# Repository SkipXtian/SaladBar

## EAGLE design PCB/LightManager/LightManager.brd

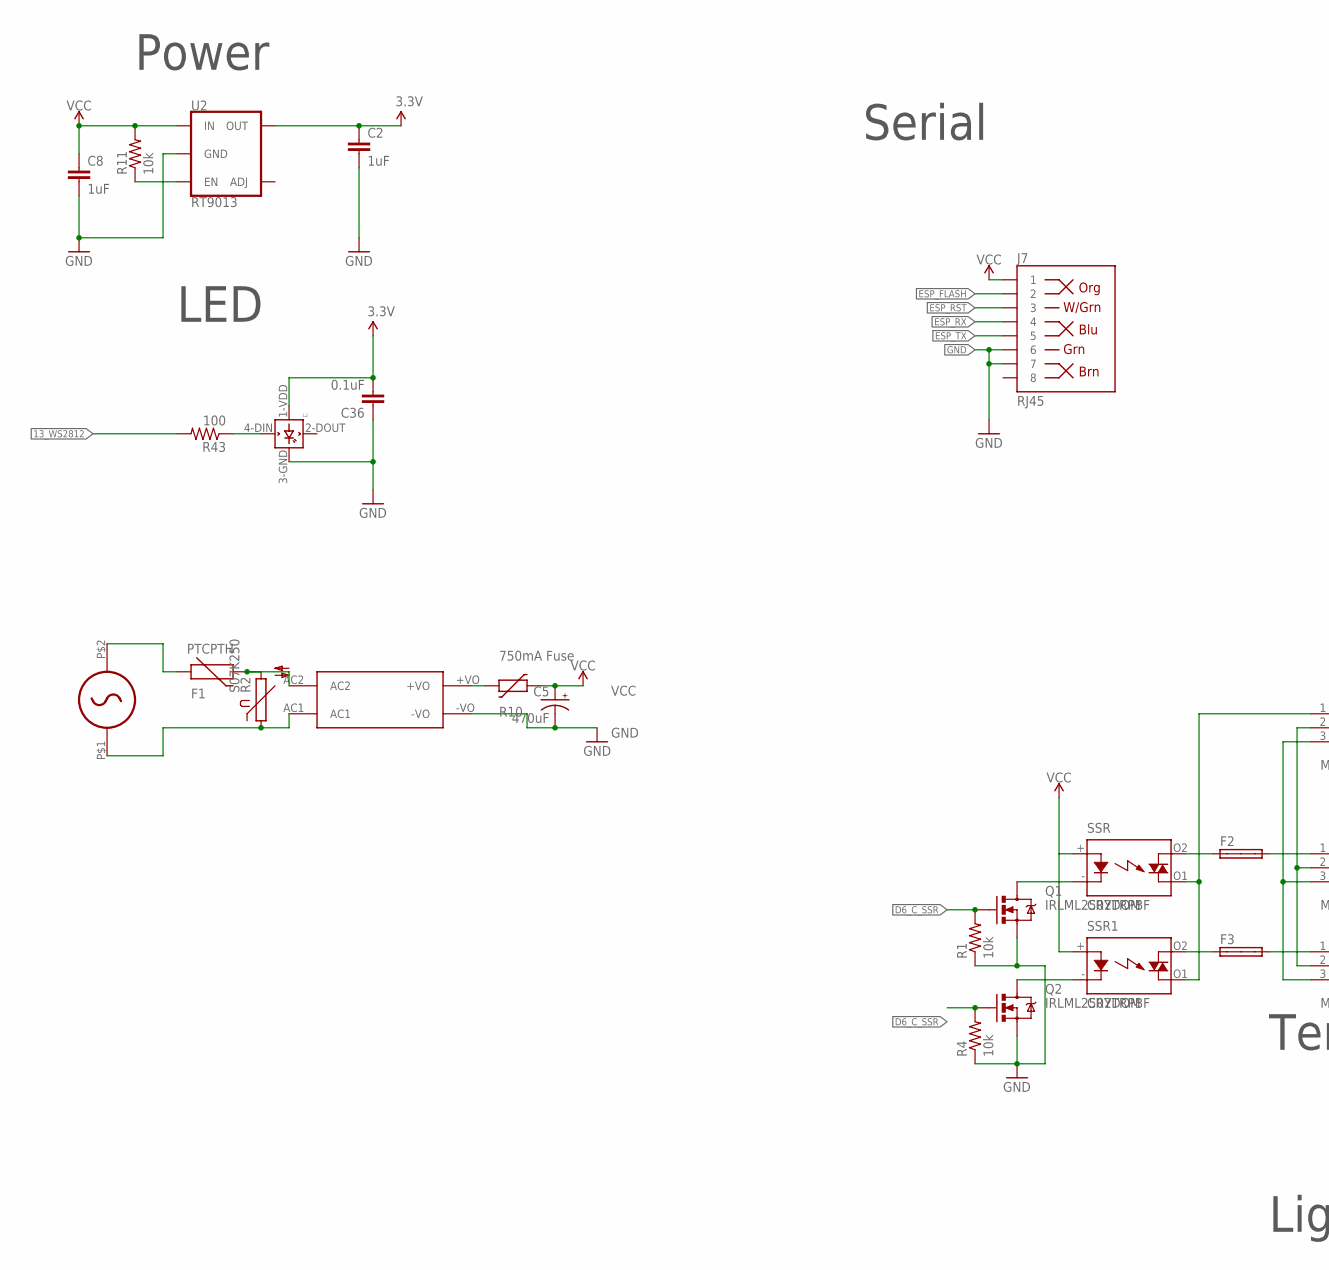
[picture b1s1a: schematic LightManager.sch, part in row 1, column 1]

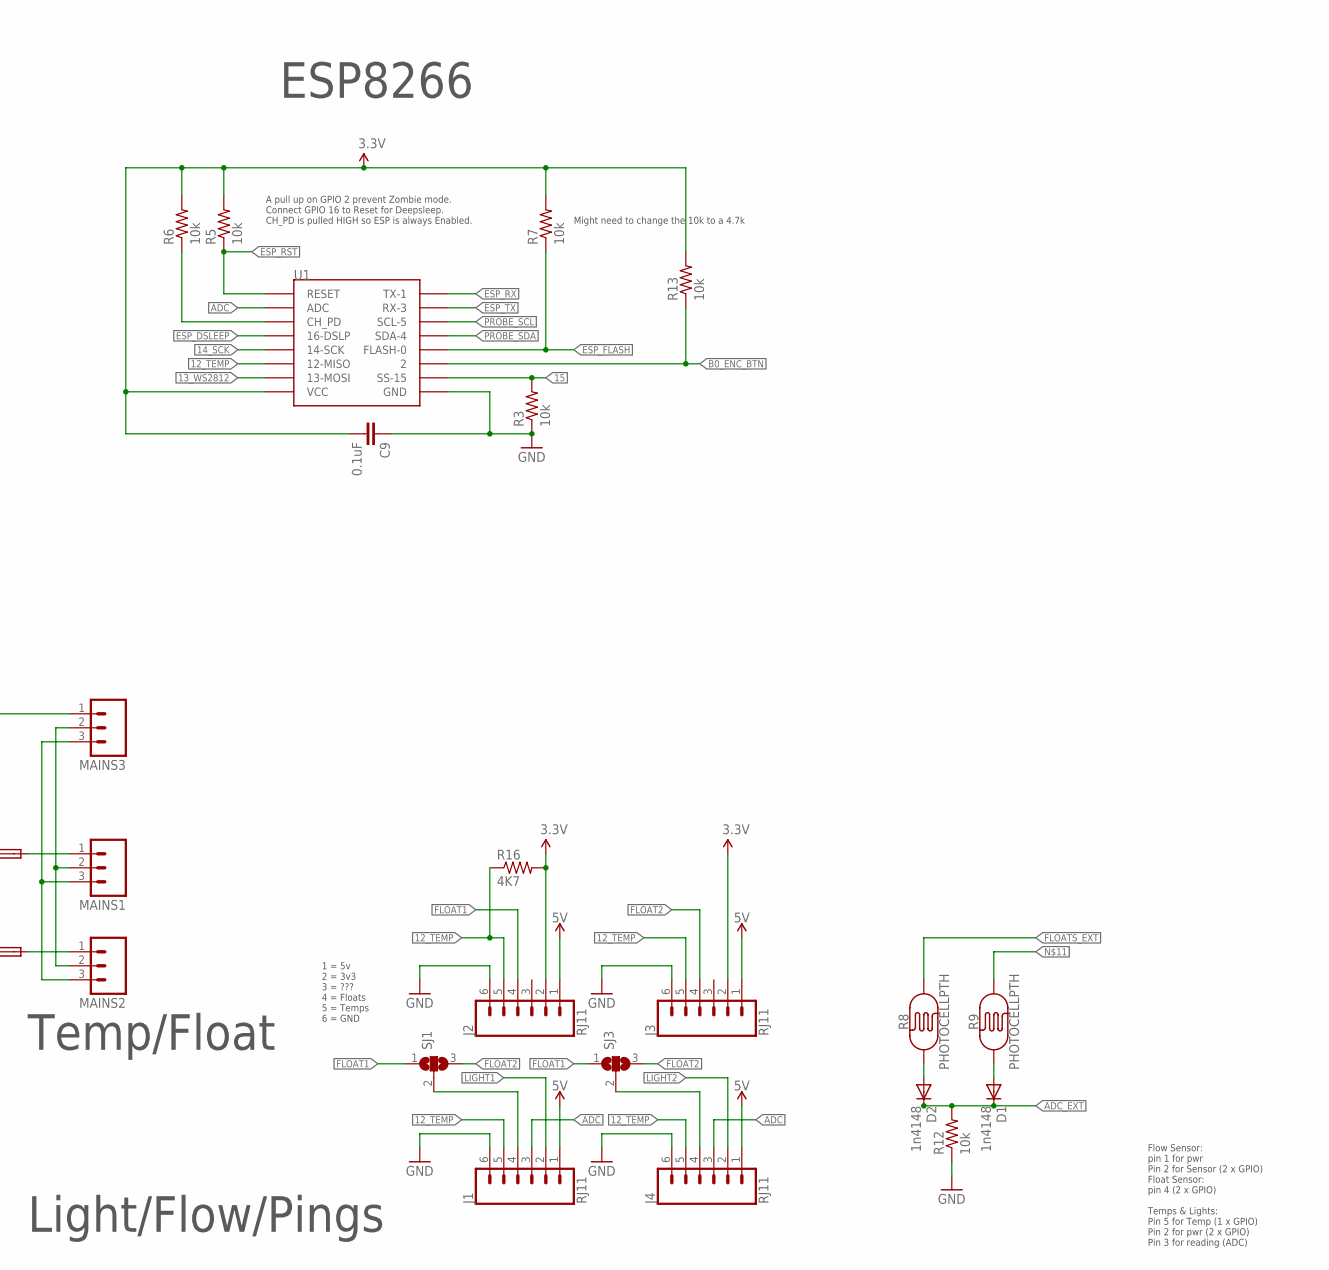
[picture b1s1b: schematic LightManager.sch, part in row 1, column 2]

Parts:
C2, C8: 1uF; 0805
C5: 470uF; PANASONIC_E
C9, C36: 0.1uF; 0805
D1, D2: 1n4148; SOD-323
F1: PTCPTH; PTC
F2, F3: SHK20L
J1, J2, J3, J4: RJ11; RJ11-6
J7: RJ45; RJ45-8
L2: WS2812B
MAINS1, MAINS2, MAINS3: M03-SCREW-5MM; SCREWTERMINAL-5MM-3
Q1, Q2: IRLML2502TRPBF; SOT23-3
R1, R3, R4, R5, R6, R7, R11, R12, R13: 10k; 0805
R2: S07K250
R8, R9: PHOTOCELLPTH; PHOTOCELL
R10: 750mA Fuse; CT/CN0805
R16: 4K7; 0805
R43: 100; 0805
SJ1, SJ3: SJ2W; SJ_2
SSR: CRYDOM; AQG
SSR1: CRYDOM; AQG; MPN AQG22224
U1: ESP12SMD; ESP12-SMD
U2: RT9013; SOT23-5
U$1: HLK-PM01
U$9: IEC320-C8

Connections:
3.3V: J2.2, J3.2, R16.2
5V: J1.1, J2.1, J3.1, J4.1
12_TEMP: J1.5, J2.5, J3.5, J4.5, R16.1, U1.GPIO12 (12-MISO)
13_WS2812: R43.2, U1.GPIO13 (13-MOSI)
14_SCK: U1.GPIO14 (14-SCK)
15: R3.2, U1.GPIO15 (SS-15)
ADC: J1.3, J4.3, U1.ADC
ADC_EXT: D1.1 (C), D2.1 (C), R12.2
B0_ENC_BTN: R13.1, U1.GPIO2 (2)
D6_C_SSR: Q1.1 (G), Q2.1 (G), R1.2, R4.2
ESP_3.3V: C2.1, C9.2, C36.2, L2.1-VDD (VDD), R5.2, R6.2, R7.2, R13.2, U1.VCC, U2.5 (OUT)
ESP_DSLEEP: U1.GPIO16 (16-DSLP)
ESP_FLASH: J7.2, R7.1, U1.GPIO0 (FLASH-0)
ESP_GND: C9.1, C36.1, L2.3-GND (GND), R3.1, U1.GND
ESP_RST: J7.3, R5.1, U1.RESET
ESP_RX: J7.4, U1.TXD0 (TX-1)
ESP_TX: J7.5, U1.RXD0 (RX-3)
FLOAT1: J2.4, SJ1.1, SJ3.1
FLOAT2: J3.4, SJ1.3, SJ3.3
FLOATS_EXT: R8.2
GND: C2.2, C5.-, C8.2, J1.6, J2.6, J3.6, J4.6, J7.6, J7.7, Q1.2 (S), Q2.2 (S), R1.1, R4.1, R12.1, U2.2 (GND), U$1.-VO
LIGHT1: J1.2
LIGHT2: J4.2
MAIN_ACTIVE: F1.P$1 (1), MAINS3.1, SSR.O1 (DS2), SSR1.O1 (DS2), U$9.P$2
MAIN_EARTH: MAINS1.3, MAINS2.3, MAINS3.3
MAIN_NETURAL: MAINS1.2, MAINS2.2, MAINS3.2, R2.1, U$1.AC1, U$9.P$1
unnamed: R6.1, U1.CH_PD
unnamed: D2.2 (A), R8.1
unnamed: Q1.3 (D), SSR.- (K)
unnamed: Q2.3 (D), SSR1.- (K)
unnamed: D1.2 (A), R9.1
unnamed: J1.4, SJ1.2
unnamed: J4.4, SJ3.2
unnamed: F1.P$2 (2), R2.2, U$1.AC2
unnamed: R10.2, U$1.+VO
unnamed: R11.1, U2.3 (EN)
unnamed: F3.1A, SSR1.O2 (DS1)
unnamed: F2.1A, SSR.O2 (DS1)
unnamed: F2.2A, MAINS1.1
unnamed: F3.2A, MAINS2.1
unnamed: L2.4-DIN (DIN), R43.1
PROBE_SCL: U1.GPIO5 (SCL-5)
PROBE_SDA: U1.GPIO4 (SDA-4)
VCC: C5.+, C8.1, J7.1, R10.1, R11.2, SSR.+ (A), SSR1.+ (A), U2.1 (IN)

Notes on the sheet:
Temp/Float
A pull up on GPIO 2 prevent Zombie mode. Connect GPIO 16 to Reset for Deepsleep. CH_PD is pulled HIGH so ESP is always Enabled.
Might need to change the 10k to a 4.7k
LED
ESP8266
Power
Serial
1 = 5v 2 = 3v3 3 = ??? 4 = Floats 5 = Temps 6 = GND
Light/Flow/Pings
Flow Sensor: pin 1 for pwr Pin 2 for Sensor (2 x GPIO) Float Sensor: pin 4 (2 x GPIO) Temps & Lights: Pin 5 for Temp (1 x GPIO) Pin 2 for pwr (2 x GPIO) Pin 3 for reading (ADC)

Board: 2 copper layers, 45 parts (1 on the bottom side), 37 nets, no tracks yet.

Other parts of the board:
U$20: ID_LOGO_X0.25

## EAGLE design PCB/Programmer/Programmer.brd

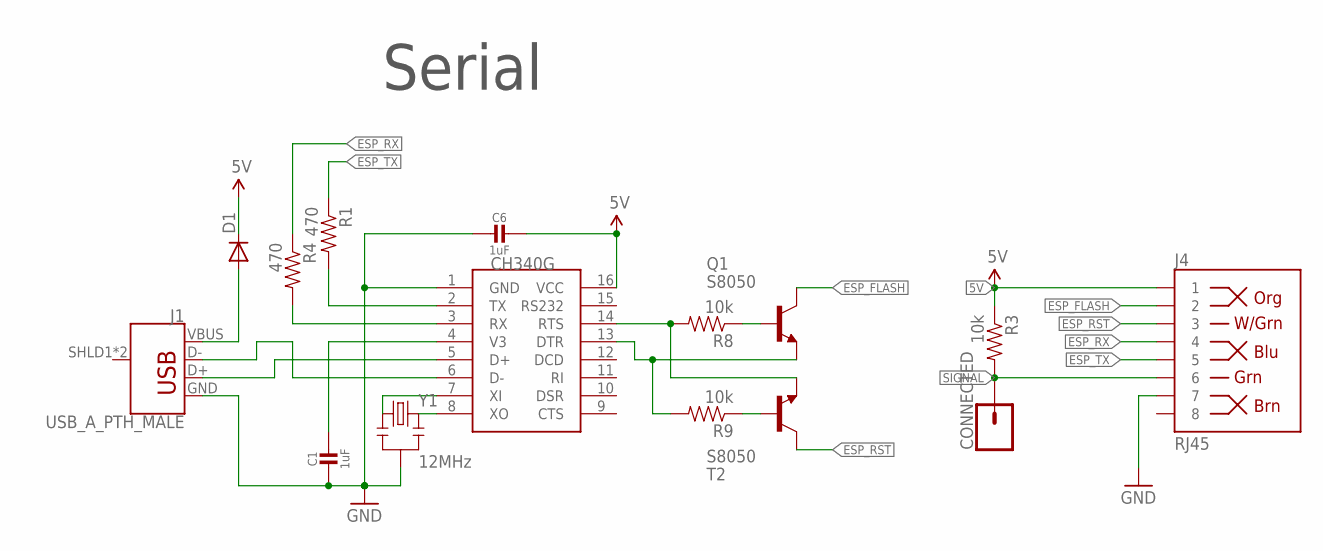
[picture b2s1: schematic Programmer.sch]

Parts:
C1, C6: 1uF; 0805-NO
CONNECTED: CONN_01; 1X01
D1: DIODESOD; SOD-323
J1: USB_A_PTH_MALE; USB-A-H
J4: RJ45; RJ45-8
Q1: S8050; SOT23-BEC
R1, R4: 470; 0805
R3, R8, R9: 10k; 0805
T2: S8050; SOT23-BEC
U$4: CH340G; SOIC16
Y1: 12MHz; RESONATOR-SMD

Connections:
5V: C6.1, D1.1 (C), J4.1, R3.1, U$4.16 (VCC)
ESP_FLASH: J4.2, Q1.C
ESP_RST: J4.3, T2.C
ESP_RX: J4.4, R4.1
ESP_TX: J4.5, R1.1
GND: C1.2, C6.2, J1.GND, J4.7, U$4.1 (GND), Y1.2
unnamed: C1.1, U$4.4 (V3)
unnamed: U$4.8 (XO), Y1.3
unnamed: J1.D-, U$4.6 (D-)
unnamed: J1.D+, U$4.5 (D+)
unnamed: R8.2, T2.E, U$4.14 (RTS)
unnamed: U$4.7 (XI), Y1.1
unnamed: R4.2, U$4.3 (RX)
unnamed: R1.2, U$4.2 (TX)
unnamed: Q1.B, R8.1
unnamed: R9.1, T2.B
unnamed: Q1.E, R9.2, U$4.13 (DTR)
SIGNAL: CONNECTED.1, J4.6, R3.2
VBUS1: D1.2 (A), J1.VBUS

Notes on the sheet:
Serial

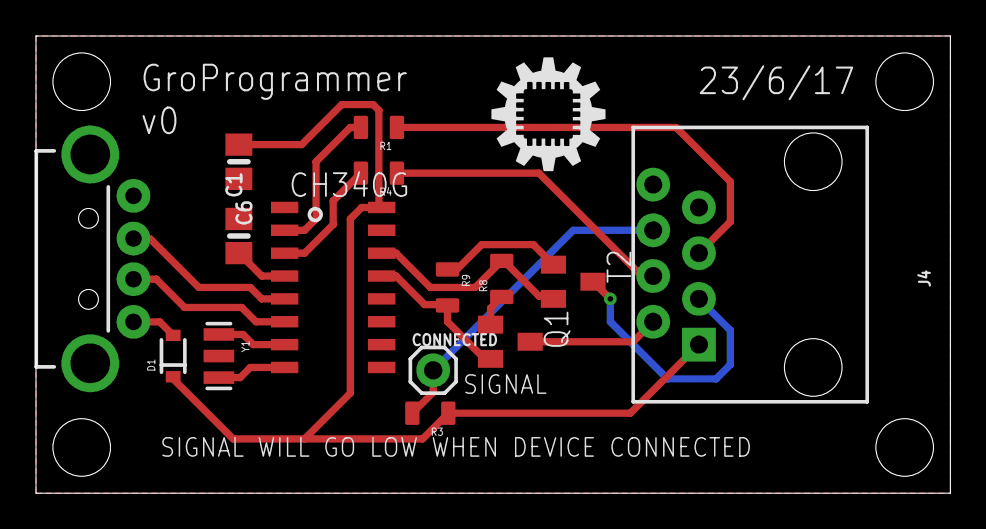
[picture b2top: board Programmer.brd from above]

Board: 2 copper layers, 50.8 x 25.4 mm, 17 parts (0 on the bottom side), 19 nets.

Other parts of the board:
U$1, U$20: ID_LOGO_X0.25

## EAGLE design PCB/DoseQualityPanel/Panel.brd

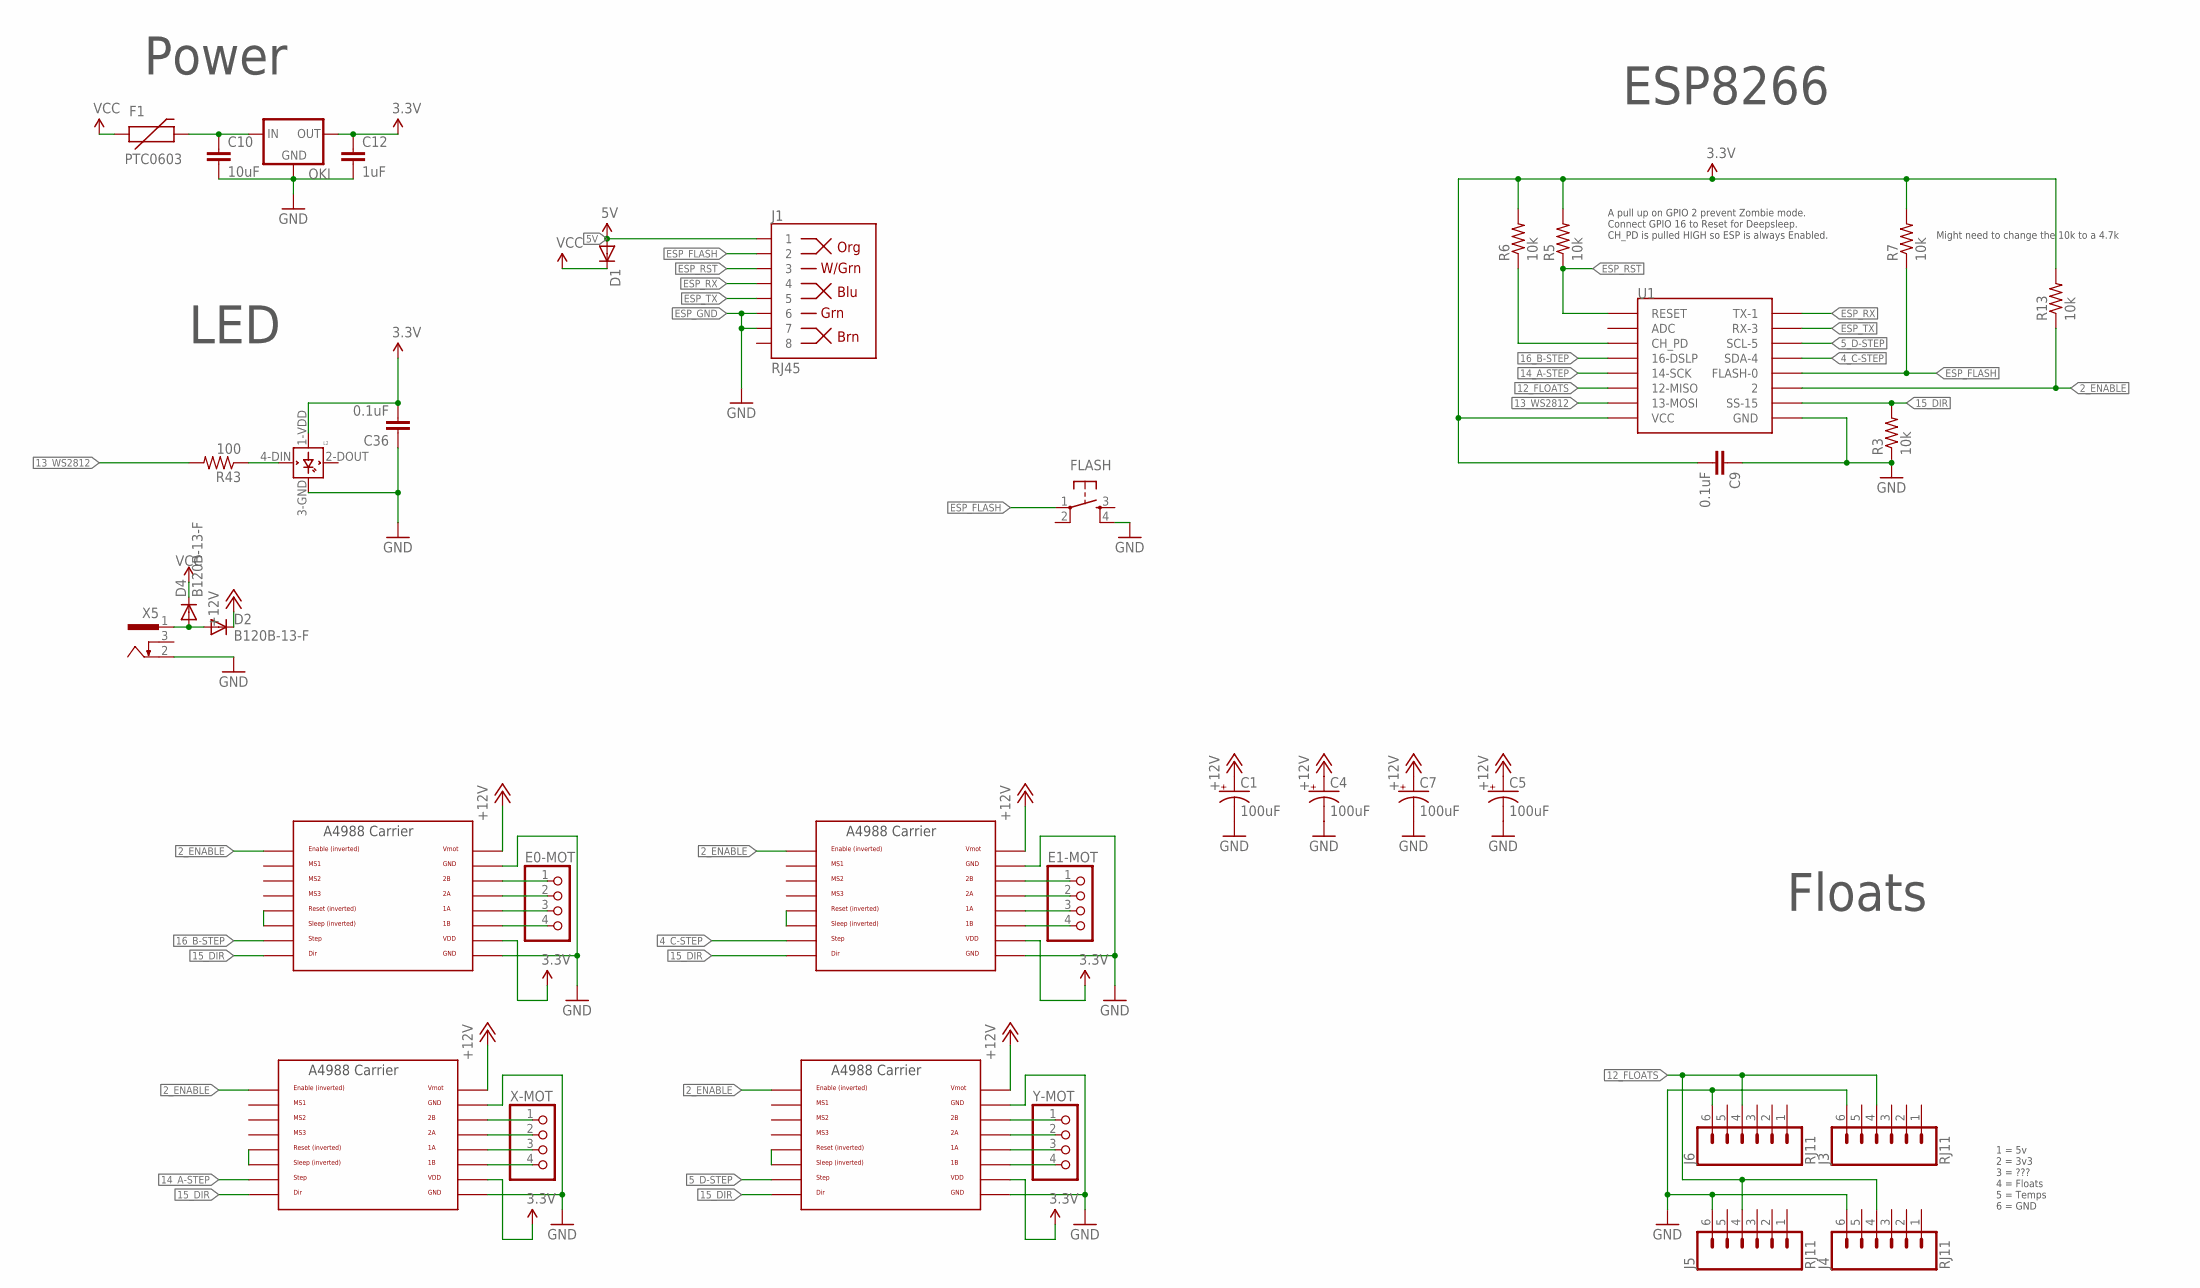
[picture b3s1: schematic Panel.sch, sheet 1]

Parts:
C1, C4, C5, C7: 100uF; 153CLV-0605
C9, C36: 0.1uF; 0805
C10: 10uF; 1206
C12: 1uF; 0805
D1: DIODESOD; SOD-323
D2, D4: B120B-13-F; SMB-DIODE
E0-MOT, E1-MOT: PINHD-1X4; 1X04
F1: PTC0603; 0603
FLASH: TAC_SWITCHSMD; TACTILE_SWITCH_SMD
J1: RJ45; RJ45-8
J3, J4, J5, J6: RJ11; RJ11-6
L2: WS2812B
OKI: 78XXS
R3, R5, R6, R7, R13: 10k; 0805
R43: 100; 0805
U1: ESP12SMD; ESP12-SMD
U$1, U$5, U$6, U$7: A4988BREAKOUT
U$2: LOGO_GROBOTICS-S; GROBOTICS-S
X5: 733980-62
X-MOT: PINHD-1X4; 1X04
Y-MOT: PINHD-1X4; 1X04

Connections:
2_ENABLE: R13.1, U1.GPIO2 (2), U$1.EN, U$5.EN, U$6.EN, U$7.EN
4_C-STEP: U1.GPIO4 (SDA-4), U$5.STEP
5V: D1.2 (A), J1.1
5_D-STEP: U1.GPIO5 (SCL-5), U$7.STEP
12_FLOATS: J3.4, J4.4, J5.4, J6.4, U1.GPIO12 (12-MISO)
13_WS2812: R43.2, U1.GPIO13 (13-MOSI)
14_A-STEP: U1.GPIO14 (14-SCK), U$6.STEP
15_DIR: R3.2, U1.GPIO15 (SS-15), U$1.DIR, U$5.DIR, U$6.DIR, U$7.DIR
16_B-STEP: U1.GPIO16 (16-DSLP), U$1.STEP
+12V: C1.+, C4.+, C5.+, C7.+, D2.C, U$1.VMOT, U$5.VMOT, U$6.VMOT, U$7.VMOT
ESP_3.3V: C9.2, C12.1, C36.2, L2.1-VDD (VDD), OKI.OUT, R5.2, R6.2, R7.2, R13.2, U1.VCC, U$1.VDD, U$5.VDD, U$6.VDD, U$7.VDD
ESP_FLASH: FLASH.1, J1.2, R7.1, U1.GPIO0 (FLASH-0)
ESP_GND: C1.-, C4.-, C5.-, C7.-, C9.1, C10.2, C12.2, C36.1, FLASH.4, J1.6, J1.7, J3.6, J4.6, J5.6, J6.6, L2.3-GND (GND), OKI.GND, R3.1, U1.GND, U$1.GND, U$1.GND@0 (GND), U$5.GND, U$5.GND@0 (GND), U$6.GND, U$6.GND@0 (GND), U$7.GND, U$7.GND@0 (GND), X5.2
ESP_RST: J1.3, R5.1, U1.RESET
ESP_RX: J1.4, U1.TXD0 (TX-1)
ESP_TX: J1.5, U1.RXD0 (RX-3)
unnamed: R6.1, U1.CH_PD
unnamed: D2.A, D4.A, X5.1
unnamed: U$1.RST, U$1.SLP (SLEEP)
unnamed: E0-MOT.1, U$1.2B
unnamed: U$6.RST, U$6.SLP (SLEEP)
unnamed: E0-MOT.2, U$1.2A
unnamed: E0-MOT.3, U$1.1A
unnamed: U$7.RST, U$7.SLP (SLEEP)
unnamed: U$5.RST, U$5.SLP (SLEEP)
unnamed: E0-MOT.4, U$1.1B
unnamed: E1-MOT.1, U$5.2B
unnamed: E1-MOT.2, U$5.2A
unnamed: E1-MOT.3, U$5.1A
unnamed: E1-MOT.4, U$5.1B
unnamed: U$6.2B, X-MOT.1
unnamed: U$6.2A, X-MOT.2
unnamed: U$6.1A, X-MOT.3
unnamed: U$6.1B, X-MOT.4
unnamed: U$7.2B, Y-MOT.1
unnamed: U$7.2A, Y-MOT.2
unnamed: U$7.1A, Y-MOT.3
unnamed: U$7.1B, Y-MOT.4
unnamed: C10.1, F1.2, OKI.IN
unnamed: L2.4-DIN (DIN), R43.1
VCC: D1.1 (C), D4.C, F1.1

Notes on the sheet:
Floats
A pull up on GPIO 2 prevent Zombie mode. Connect GPIO 16 to Reset for Deepsleep. CH_PD is pulled HIGH so ESP is always Enabled.
Might need to change the 10k to a 4.7k
LED
ESP8266
Power
1 = 5v 2 = 3v3 3 = ??? 4 = Floats 5 = Temps 6 = GND

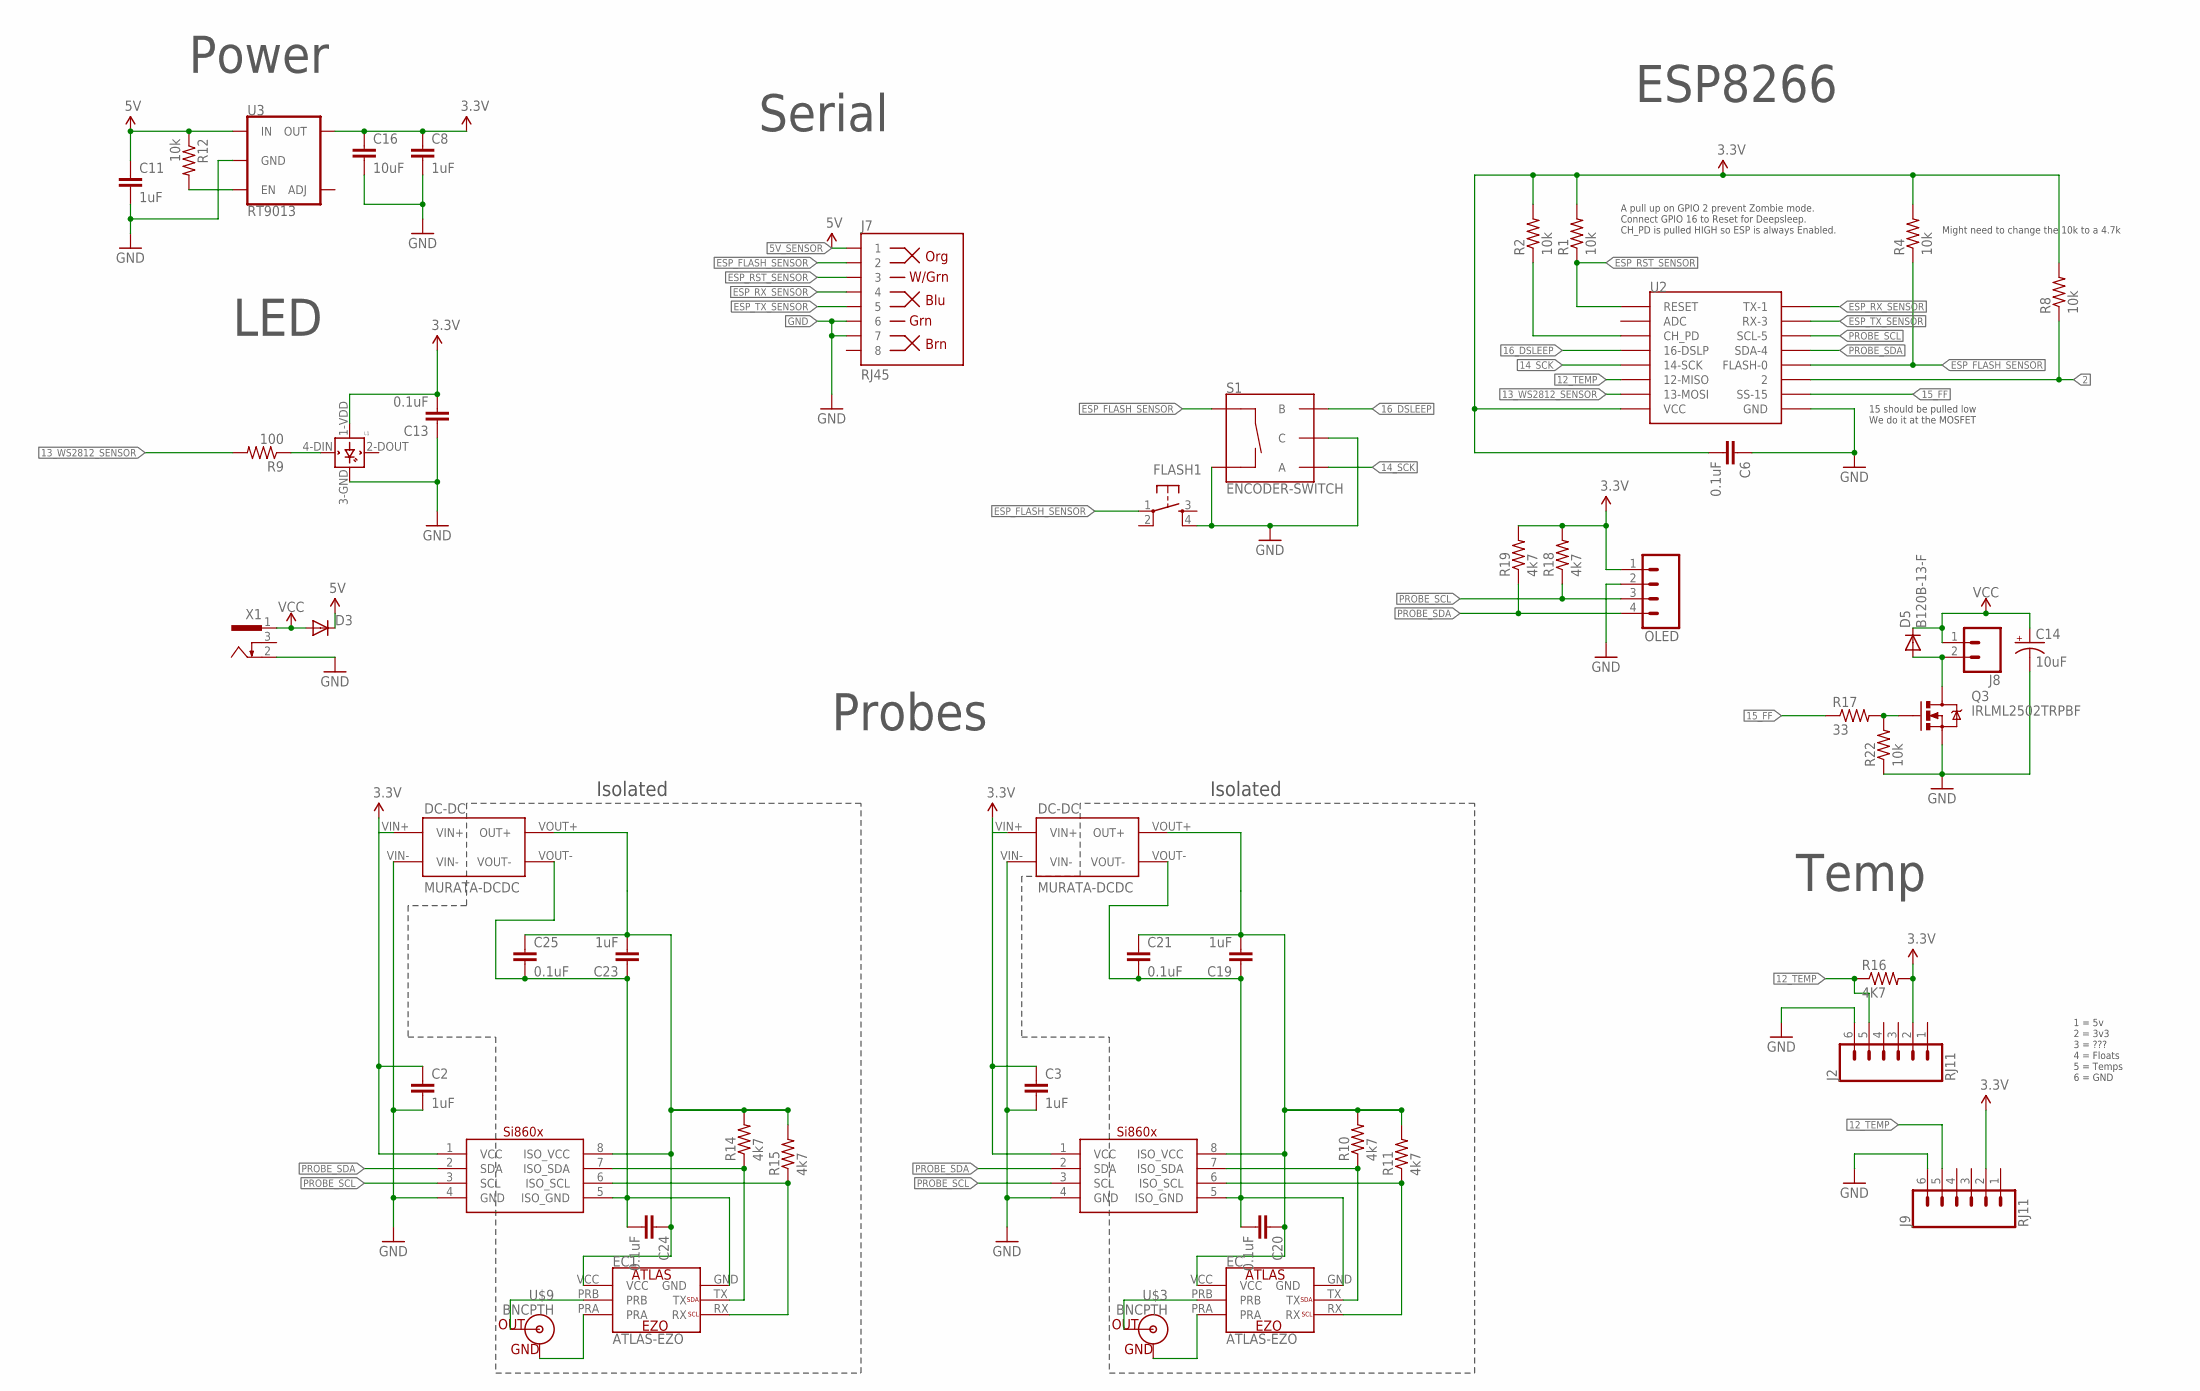
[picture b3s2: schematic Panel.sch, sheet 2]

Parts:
C2, C3, C8, C11, C19, C23: 1uF; 0805
C6, C13, C20, C21, C24, C25: 0.1uF; 0805
C14: 10uF; 153CLV-0405
C16: 10uF; 0805
D3: DIODESOD; SOD-323
D5: B120B-13-F; SMB-DIODE
EC, EC1: ATLAS-EZO
FLASH1: TAC_SWITCHSMD; TACTILE_SWITCH_SMD
J2, J9: RJ11; RJ11-6
J7: RJ45; RJ45-8
J8: CONN_02; 1X02
L1: WS2812B
OLED: CONN_04; 1X04
Q3: IRLML2502TRPBF; SOT23-3
R1, R2, R4, R8, R12, R22: 10k; 0805
R9: 100; 0805
R10, R11, R14, R15, R18, R19: 4k7; 0805
R16: 4K7; 0805
R17: 33; 0805
S1: ENCODER-SWITCH; ROTARY_ENC_PLAIN
U2: ESP12SMD; ESP12-SMD
U3: RT9013; SOT23-5
U$3, U$9: BNCPTH; BNC
U$4, U$14: MURATA-DCDC; MURATA_DCDC
U$8, U$11: SI860X; SO08
U$12: LOGO_GROBOTICS; GROBOTICS
X1: 733980-62

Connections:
2: R8.1, U2.GPIO2 (2)
3.3V: C2.1, C3.1, C6.2, C8.1, C13.2, C16.1, J2.2, J9.2, L1.1-VDD (VDD), OLED.1, R1.2, R2.2, R4.2, R8.2, R16.2, R18.2, R19.2, U2.VCC, U3.5 (OUT), U$4.VIN+, U$8.1 (VCC), U$11.1 (VCC), U$14.VIN+
5V_SENSOR: C11.1, D3.1 (C), J7.1, R12.1, U3.1 (IN)
12_TEMP: J2.5, J9.5, R16.1, U2.GPIO12 (12-MISO)
13_WS2812_SENSOR: R9.2, U2.GPIO13 (13-MOSI)
14_SCK: S1.A, U2.GPIO14 (14-SCK)
15_FF: R17.1, U2.GPIO15 (SS-15)
16_DSLEEP: S1.B, U2.GPIO16 (16-DSLP)
ESP_FLASH_SENSOR: FLASH1.1, J7.2, R4.1, S1.SW+, U2.GPIO0 (FLASH-0)
ESP_RST_SENSOR: J7.3, R1.1, U2.RESET
ESP_RX_SENSOR: J7.4, U2.TXD0 (TX-1)
ESP_TX_SENSOR: J7.5, U2.RXD0 (RX-3)
GND: C2.2, C3.2, C6.1, C8.2, C11.2, C13.1, C14.-, C16.2, FLASH1.4, J2.6, J7.6, J7.7, J9.6, L1.3-GND (GND), OLED.2, Q3.2 (S), R22.1, S1.C, S1.SW-, U2.GND, U3.2 (GND), U$4.VIN-, U$8.4 (GND), U$11.4 (GND), U$14.VIN-, X1.2
unnamed: EC.PRB, U$3.S (OUT)
unnamed: EC1.PRB, U$9.S (OUT)
unnamed: EC1.PRA, U$9.GND
unnamed: EC1.RX, R15.1, U$11.6 (ISO_SCL)
unnamed: EC1.TX, R14.1, U$11.7 (ISO_SDA)
unnamed: EC.PRA, U$3.GND
unnamed: R2.1, U2.CH_PD
unnamed: L1.4-DIN (DIN), R9.1
unnamed: EC.RX, R11.1, U$8.6 (ISO_SCL)
unnamed: R12.2, U3.3 (EN)
unnamed: EC.TX, R10.1, U$8.7 (ISO_SDA)
unnamed: C19.1, C20.2, C21.2, EC.GND, U$4.VOUT-, U$8.5 (ISO_GND)
unnamed: C19.2, C20.1, C21.1, EC.VCC, R10.2, R11.2, U$4.VOUT+ (OUT+), U$8.8 (ISO_VCC)
unnamed: C23.1, C24.2, C25.2, EC1.GND, U$11.5 (ISO_GND), U$14.VOUT-
unnamed: Q3.1 (G), R17.2, R22.2
unnamed: C23.2, C24.1, C25.1, EC1.VCC, R14.2, R15.2, U$11.8 (ISO_VCC), U$14.VOUT+ (OUT+)
unnamed: D5.A, J8.2, Q3.3 (D)
PROBE_SCL: OLED.3, R18.1, U2.GPIO5 (SCL-5), U$8.3 (SCL), U$11.3 (SCL)
PROBE_SDA: OLED.4, R19.1, U2.GPIO4 (SDA-4), U$8.2 (SDA), U$11.2 (SDA)
VCC_SENSOR: C14.+, D3.2 (A), D5.C, J8.1, X1.1

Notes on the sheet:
Isolated
Probes
Temp
A pull up on GPIO 2 prevent Zombie mode. Connect GPIO 16 to Reset for Deepsleep. CH_PD is pulled HIGH so ESP is always Enabled.
Might need to change the 10k to a 4.7k
LED
ESP8266
Power
Serial
15 should be pulled low We do it at the MOSFET
1 = 5v 2 = 3v3 3 = ??? 4 = Floats 5 = Temps 6 = GND

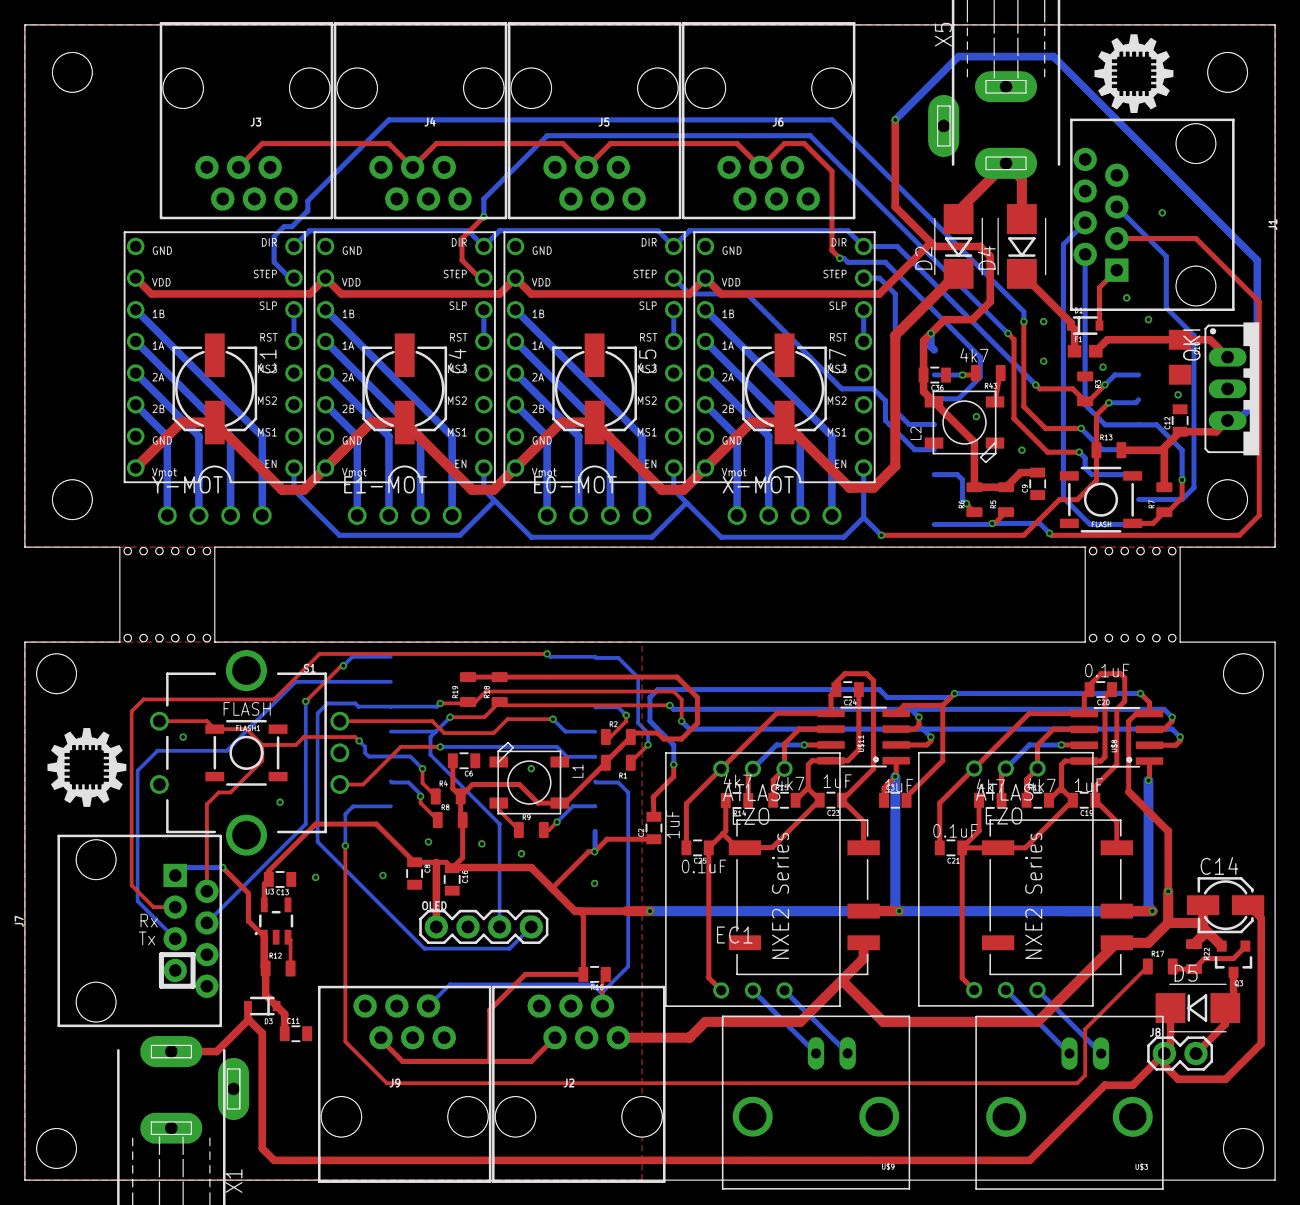
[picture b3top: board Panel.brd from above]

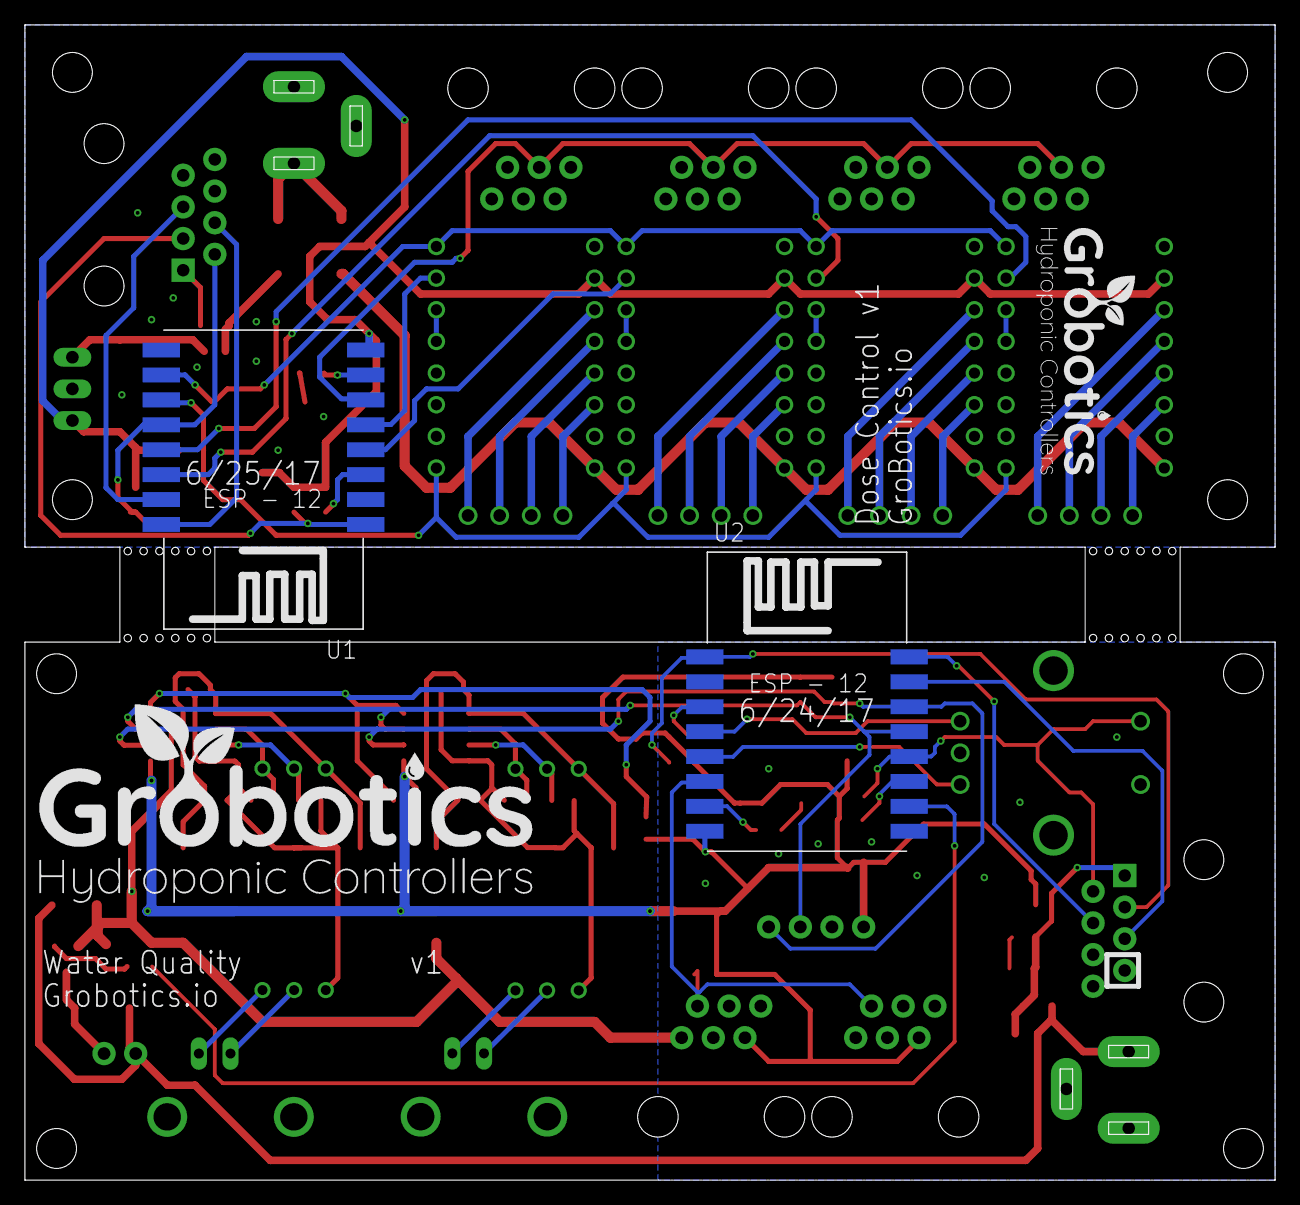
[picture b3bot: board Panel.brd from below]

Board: 2 copper layers, 100.3 x 92.7 mm, 91 parts (4 on the bottom side), 74 nets.

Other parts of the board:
U$13, U$20: ID_LOGO_X0.25

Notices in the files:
parts and their libraries:
SparkFun-Capacitors: Licensing: CC v3.0 Share-Alike You are welcome to use this library for commercial purposes.
SparkFun-IC-Power: Licensing: Creative Commons ShareAlike 4.0 International - https://creativecommons.org/licenses/by-sa/4.0
